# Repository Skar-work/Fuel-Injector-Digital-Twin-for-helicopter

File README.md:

# HAL LUH(light Utility helicopter) - Fuel Injection System Digital Twin

This project is an interactive, browser-based digital twin simulating the fuel injection system of a HAL LUH helicopter. It provides a real-time visualization of the system's parameters, flight dynamics, and responses to various fault conditions. The entire simulation runs on the client-side using vanilla JavaScript, HTML, and CSS.

**PREVIEW**

## Features

* **Real-time Physics Simulation:** The core of the digital twin is a JavaScript-based simulation that models flight dynamics4. 3D Model of board, engine parameters, and fuel system behavior at a rate of 10 Hz.
* **Interactive Controls:** Users can directly control the helicopter's flight by adjusting the **Collective Pitch** and observe the immediate effects on all system parameters.
* **Comprehensive Data Visualization:**
    * **Live Graphs:** Five real-time charts dynamically display key metrics such as Altitude, Fuel Pressure, Engine RPM, Fuel Flow Rate, and Fuel Temperature.
    * **2D System Schematic:** An interactive SVG schematic shows the status of each component in the fuel system, with visual cues for active states and faults.
    * **3D System View:** A 3D representation of the fuel system components, built with Three.js, allows for interactive exploration.
* **Advanced Fault Injection System:**
    * Manually inject faults like **Clogged Injectors**, **Fuel Overheat**, **RPM Droop**, and **Sensor Drift** to study system resilience and behavior under stress.
* **Audible & Visual Warning System:** The simulation includes a master warning system with audible voice alerts ("Warning, Warning...") and visual indicators for active faults.
* **AI-Powered Predictive Analysis :** When a fault is injected, a dedicated panel provides a detailed analysis, including:
    * Faults Detected
    * Fault Location / Systems Affected
    * Immediate Corrective Measures
    * Preferable Long-term Measures
* **Data Logging:** All simulation parameters can be recorded and downloaded as a `.csv` file for offline analysis and record-keeping.

## Tech Stack

* **Frontend:** HTML5, CSS3, Vanilla JavaScript (ES6 Classes)
* **Charting:** [Chart.js](https://www.chartjs.org/) for real-time data visualization.
* **3D Graphics:** [Three.js](https://threejs.org/) for the interactive 3D schematic.

## Project Structure

The project is entirely client-side and requires no backend or build steps.

/
├── index.html      # The main HTML file for the dashboard UI
├── style.css       # All styling for the application
└── app.js          # Core JavaScript file containing the entire simulation logic
/
└── mlbackend(not required for running the project, it was used to simulate the noise factor to mimic real world scenario)

## How to Run

This project is designed to run directly in any modern web browser.

1.  Clone or download the repository to your local machine.
2.  Navigate to the project folder in any IDE.
3.  Open the `index.html` file and run using Live-Server(VS code extension).

The digital twin dashboard will open and be fully functional.

## How to Use the Simulation

1.  **Start the Engine:** Click the `START ENGINE` button to begin the simulation.
2.  **Control Flight:** Use the **Collective Pitch** slider to increase or decrease engine power, which will affect the helicopter's altitude.
3.  **Monitor Parameters:** Observe the real-time data on the digital readouts and the live graphs.
4.  **Inject Faults:** In the "Warnings & Alerts" panel, check any of the boxes under "Fault Injection" to introduce a fault.
5.  **Observe Predictions:** When a fault is active, view the "AI Prediction" panel for a detailed breakdown and recommended actions.
6.  **Download Data:** At any point, click the `DOWNLOAD LOG` button to save a CSV file of the simulation data up to that moment.
7.  **Control the Simulation:** Use the `PAUSE`, `PLAY`, and `RESET` buttons to control the simulation's state.

## Hardware design (IO board)
The design ideas are present under /hardware/IO board/Design Notes/ 

**1. Schematic**

**2. Configuration for STM32F042F6Px**

**3. PCB Design of board**

**4. 3D Model of board**

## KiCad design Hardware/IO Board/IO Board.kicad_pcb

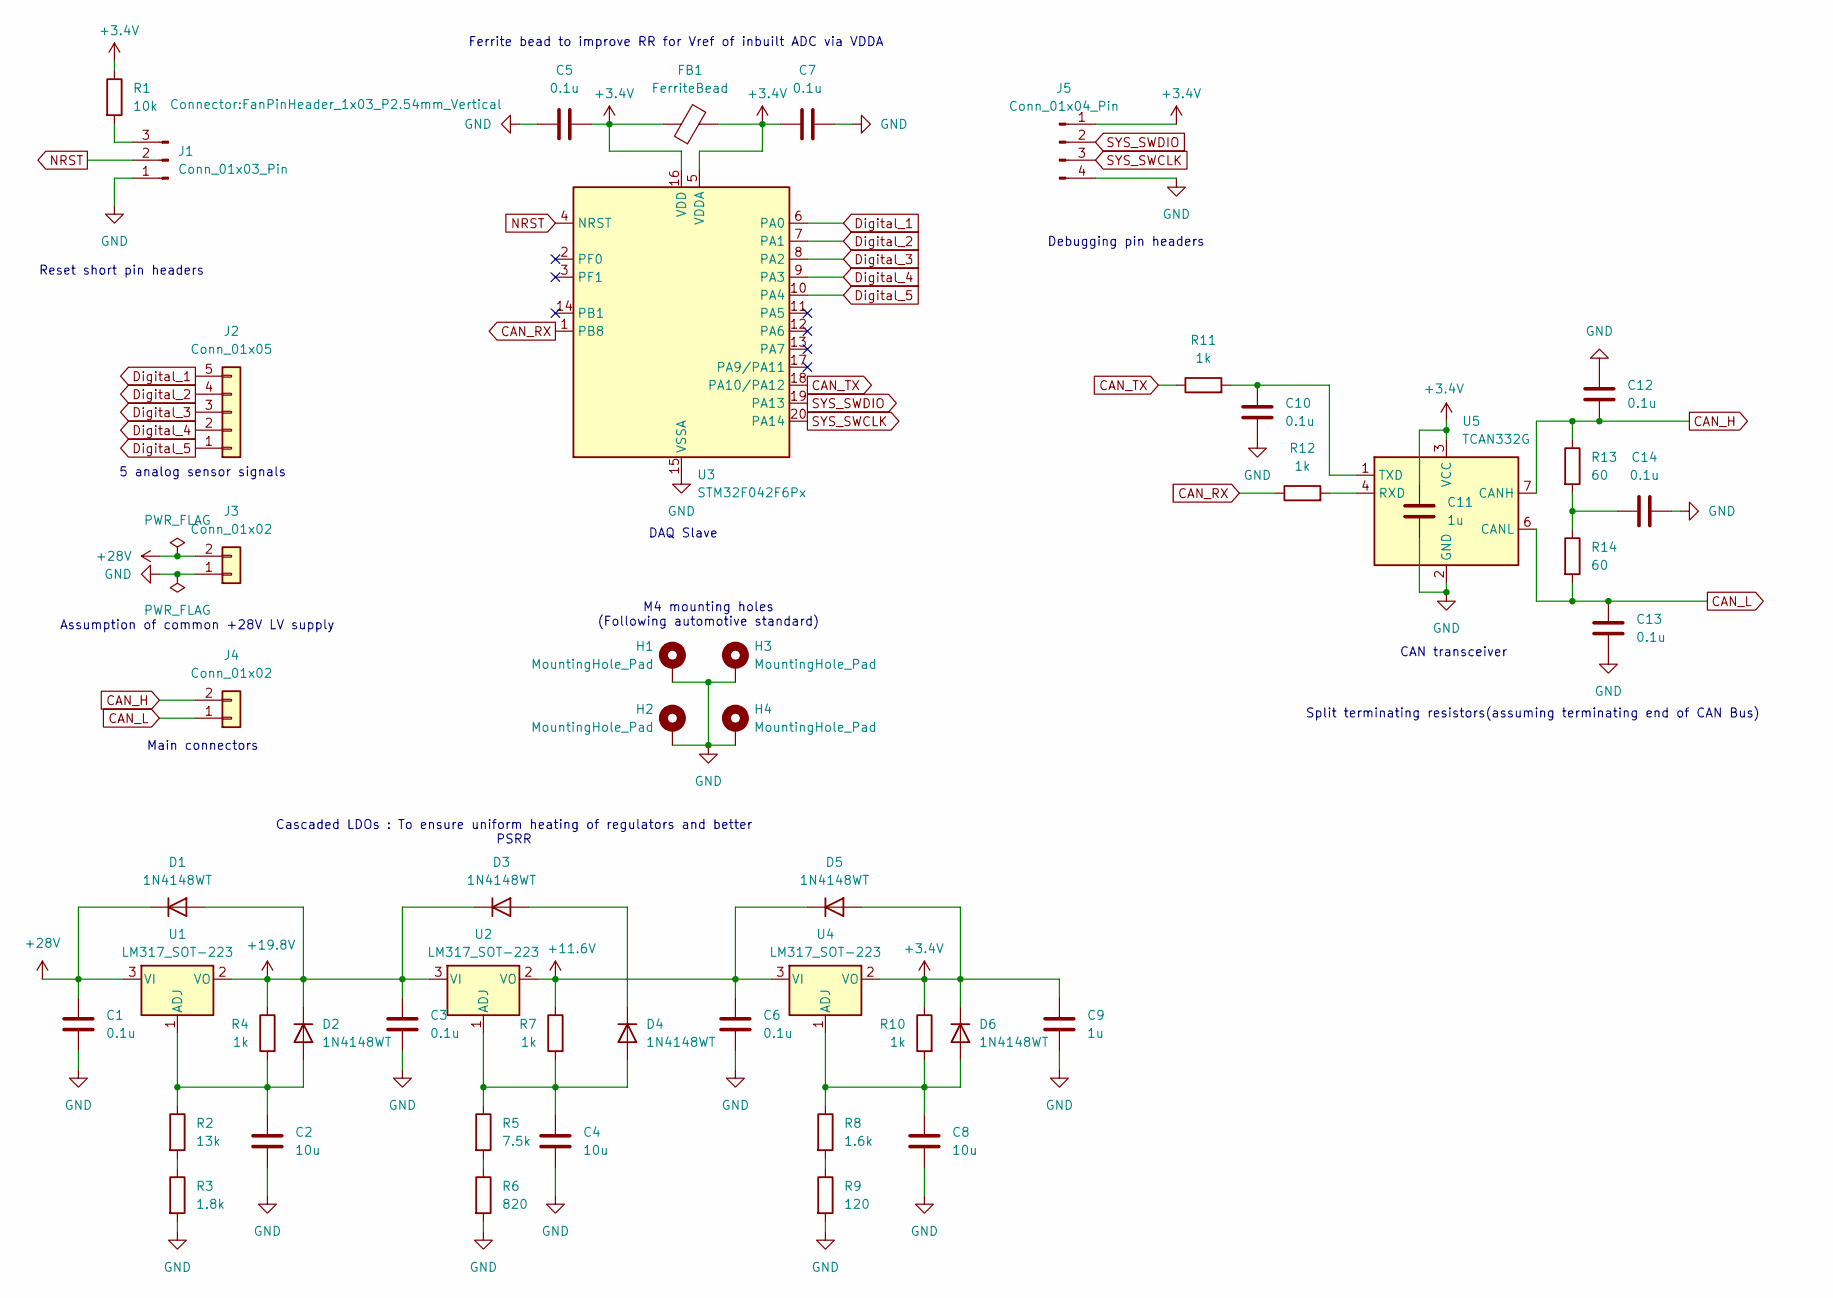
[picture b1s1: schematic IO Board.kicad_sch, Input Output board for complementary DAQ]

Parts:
C1, C3, C5, C6, C7, C10, C12, C13, C14: 0.1u; C_0603_1608Metric
C2, C4, C8: 10u; C_0603_1608Metric
C9, C11: 1u; C_0603_1608Metric
D1, D2, D3, D4, D5, D6: 1N4148WT; D_SOD-523
FB1: FerriteBead; L_0201_0603Metric
H1, H2, H3, H4: MountingHole_Pad; MountingHole_4.3mm_M4_DIN965_Pad
J1: Conn_01x03_Pin; FanPinHeader_1x03_P2.54mm_Vertical
J2: Conn_01x05; JST_XH_S5B-XH-A-1_1x05_P2.50mm_Horizontal
J3, J4: Conn_01x02; TE_440055-2_1x02_P2.00mm_Horizontal
J5: Conn_01x04_Pin; FanPinHeader_1x04_P2.54mm_Vertical
R1: 10k; R_0603_1608Metric
R2: 13k; R_0603_1608Metric
R3: 1.8k; R_0603_1608Metric
R4, R7, R10, R11, R12: 1k; R_0603_1608Metric
R5: 7.5k; R_0603_1608Metric
R6: 820; R_0603_1608Metric
R8: 1.6k; R_0603_1608Metric
R9: 120; R_0603_1608Metric
R13, R14: 60; R_0603_1608Metric
U1, U2, U4: LM317_SOT-223; SOT-223-3_TabPin2
U3: STM32F042F6Px; TSSOP-20_4.4x6.5mm_P0.65mm
U5: TCAN332G; SOIC-8_3.9x4.9mm_P1.27mm

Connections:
+3.4V: C5.2, C7.2, C9.1, C11.1, D5.2 (A), D6.1 (K), FB1.1, FB1.2, J5.1, R1.1, R10.1, U3.5 (VDDA), U3.16 (VDD), U4.2 (VO), U5.3 (VCC)
+11.6V: C6.1, D5.1 (K), R7.1, U2.2 (VO), U4.3 (VI)
+19.8V: C3.1, D1.2 (A), D2.1 (K), D3.1 (K), R4.1, U1.2 (VO), U2.3 (VI)
+28V: C1.1, D1.1 (K), J3.2, U1.3 (VI)
CAN_H: C12.1, J4.2, R13.1, U5.7 (CANH)
CAN_L: C13.1, J4.1, R14.2, U5.6 (CANL)
CAN_RX: R12.1, U3.1 (PB8)
CAN_TX: R11.1, U3.18 (PA10/PA12)
Digital_1: J2.5, U3.6 (PA0)
Digital_2: J2.4, U3.7 (PA1)
Digital_3: J2.3, U3.8 (PA2)
Digital_4: J2.2, U3.9 (PA3)
Digital_5: J2.1, U3.10 (PA4)
GND: C1.2, C2.2, C3.2, C4.2, C5.1, C6.2, C7.1, C8.2, C9.2, C10.2, C11.2, C12.2, C13.2, C14.2, H1.1, H2.1, H3.1, H4.1, J1.1, J3.1, J5.4, R3.2, R6.2, R9.2, U3.15 (VSSA), U5.2 (GND)
NRST: J1.2, U3.4 (NRST)
unnamed: C14.1, R13.2, R14.1
unnamed: C2.1, D2.2 (A), R2.1, R4.2, U1.1 (ADJ)
unnamed: D3.2 (A), D4.1 (K)
unnamed: C4.1, D4.2 (A), R5.1, R7.2, U2.1 (ADJ)
unnamed: C8.1, D6.2 (A), R8.1, R10.2, U4.1 (ADJ)
unnamed: J1.3, R1.2
unnamed: R2.2, R3.1
unnamed: R5.2, R6.1
unnamed: R8.2, R9.1
unnamed: R12.2, U5.4 (RXD)
unnamed: C10.1, R11.2, U5.1 (TXD)
SYS_SWCLK: J5.3, U3.20 (PA14)
SYS_SWDIO: J5.2, U3.19 (PA13)

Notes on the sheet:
CAN transceiver
Split terminating resistors(assuming terminating end of CAN Bus)
Reset short pin headers
Debugging pin headers
5 analog sensor signals
DAQ Slave
Cascaded LDOs : To ensure uniform heating of regulators and better PSRR
Main connectors
Ferrite bead to improve RR for Vref of inbuilt ADC via VDDA
Assumption of common +28V LV supply
M4 mounting holes (Following automotive standard)

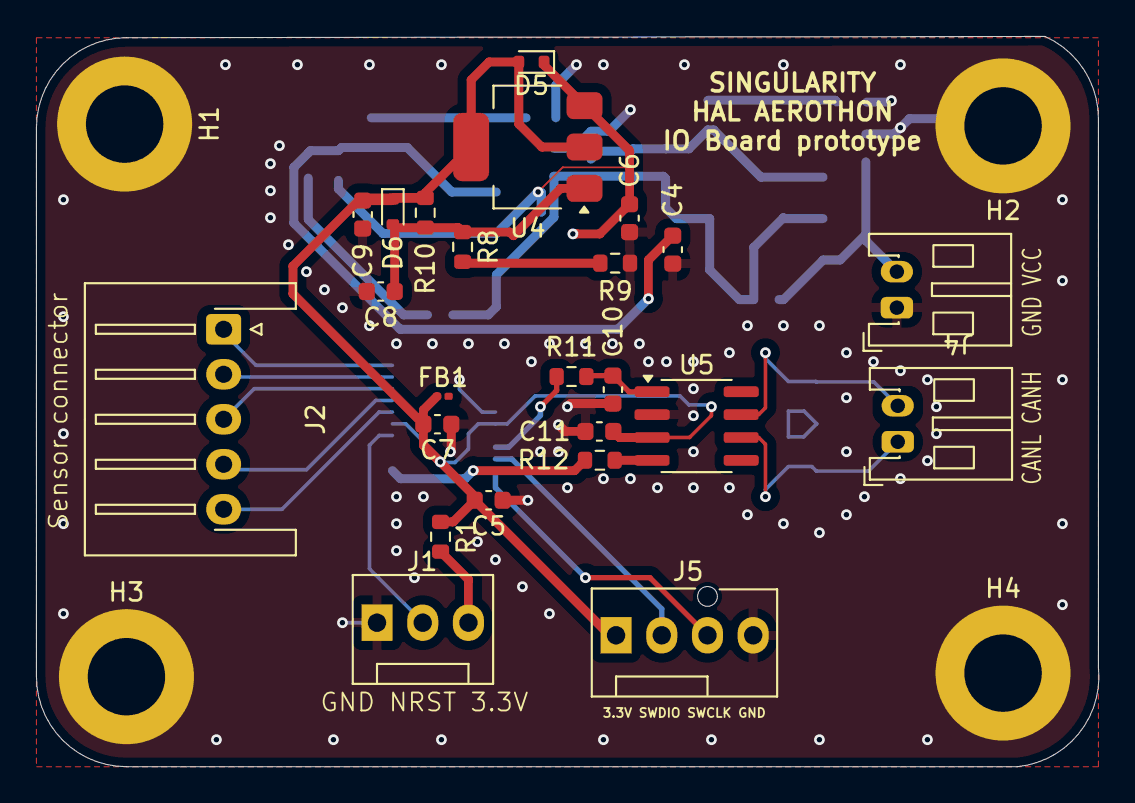
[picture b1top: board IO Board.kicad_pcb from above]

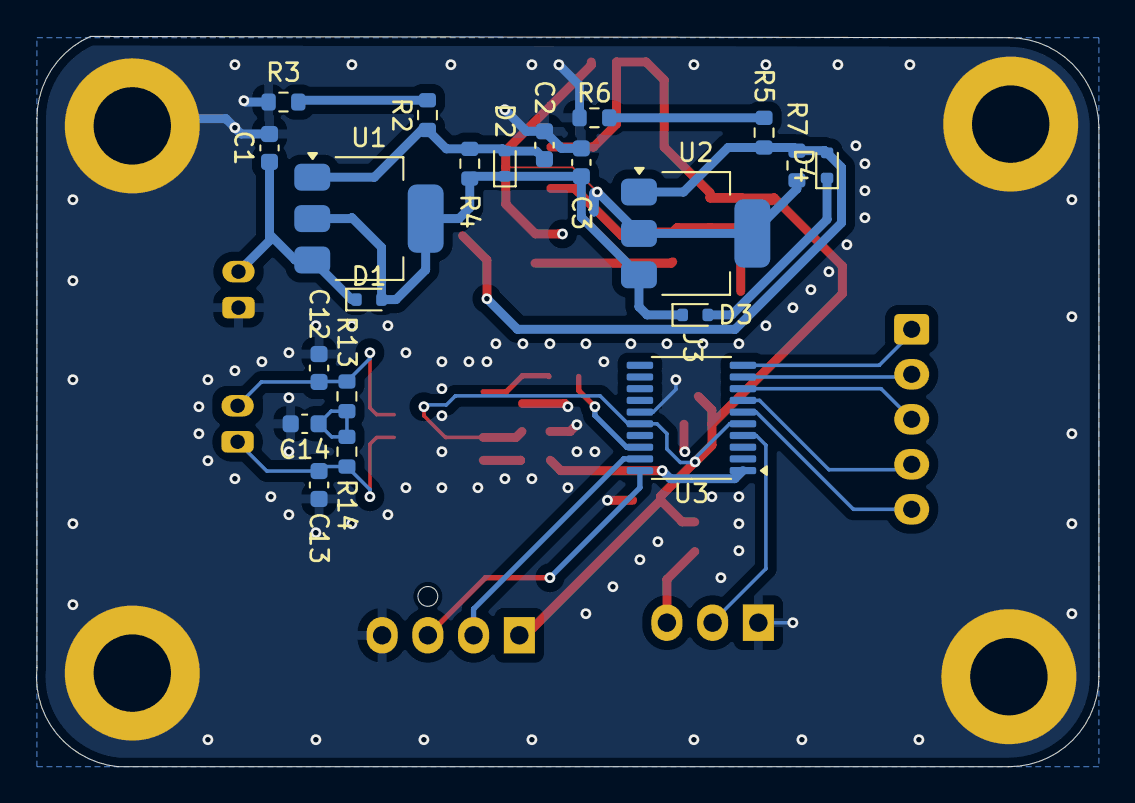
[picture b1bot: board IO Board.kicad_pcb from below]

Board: 2 copper layers, 59.0 x 40.6 mm, 49 parts (21 on the bottom side), 28 nets.

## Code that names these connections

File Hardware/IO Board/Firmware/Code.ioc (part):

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Mcu.Name=STM32F042F6Px
Mcu.Package=TSSOP20
Mcu.UserName=STM32F042F6Px
PA0.Mode=IN0
PA0.Signal=ADC_IN0
PA1.Mode=IN1
PA1.Signal=ADC_IN1
PA12.Mode=CAN_Activate
PA12.Signal=CAN_TX
PA13.Mode=Serial_Wire
PA13.Signal=SYS_SWDIO
PA14.Mode=Serial_Wire
PA14.Signal=SYS_SWCLK
PA2.Mode=IN2
PA2.Signal=ADC_IN2
PA3.Mode=IN3
PA3.Signal=ADC_IN3
PA4.Mode=IN4
PA4.Signal=ADC_IN4
PB8.Mode=CAN_Activate
PB8.Signal=CAN_RX
PF0-OSC_IN.Mode=HSE-External-Oscillator
PF0-OSC_IN.Signal=RCC_OSC_IN
PF1-OSC_OUT.Mode=HSE-External-Oscillator
PF1-OSC_OUT.Signal=RCC_OSC_OUT
board=custom

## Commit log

2025-07-21 README.md
2025-07-21 Added hardware folder
2025-07-21 Renamed IOT folder
2025-07-23 Added hardware images
